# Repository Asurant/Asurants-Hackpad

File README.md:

# Asurants-Hackpad
A simple 6 key macropad meant for day to day usage.
Is capable of going back, forward, and refreshing a browser tab and is also capable of undoing, redoing, finding words (ctrl + f).

It was made using the Blueprint Hackpad tutorial from Hack Club.
https://blueprint.hackclub.com/r/56?ref=r

CAD Model:
The CAD Model Was made in Fusion 360\

Full CAD But Different Angle:\

CAD PCB No Case:\

CAD Model Without Top:\

CAD Model Bottom:\

CAD Model Top:\

Case Without PCB (Held Together by 4 M3x16mm screws):\

The PCB Was made in Kicad.

PCB Schematic:\

PCB:\

PCB 3D Model (From Kicad):\

The Firmware was done with QMK.
Key Shortcuts (Left to Right. Top To Bottom):
\[Browser Back, Browser Forward, Refresh]
\[Undo, Redo, Ctrl+F]

Bill of Materials:\
2x SK6812 MINI-E LEDs\
6x Cherry_MX switches\
6x DSA Keycaps\
4x M3x16mm Screws\
1x XIAO RP2040\
1x Case\

BTW\
Symbol on case is the Justiciar symbol from Lord Of The Mysteries / Lord Of Mysteries / Guǐ Mì Zhī Zhǔ

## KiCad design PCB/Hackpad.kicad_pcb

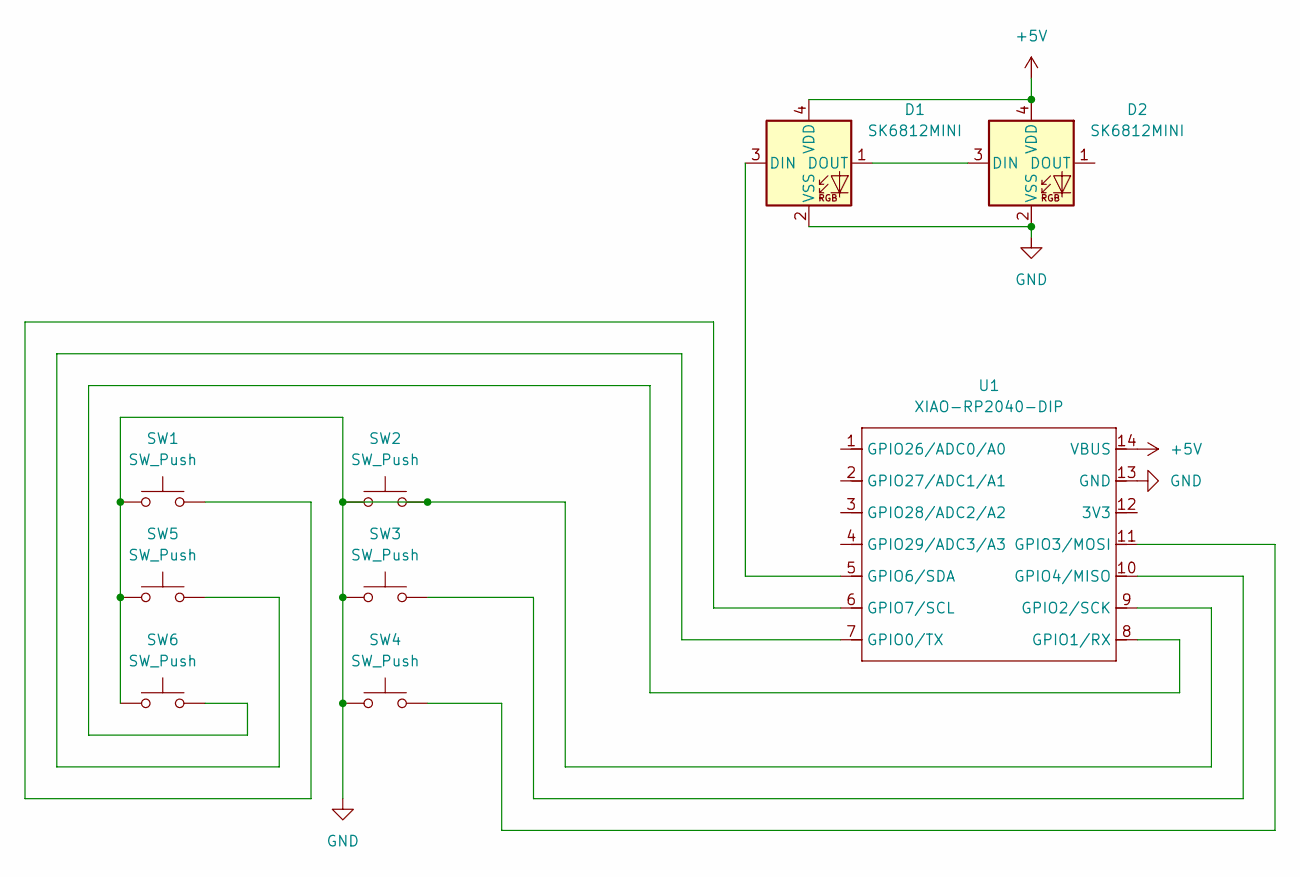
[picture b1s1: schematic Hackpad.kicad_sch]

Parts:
D1, D2: SK6812MINI; LED_SK6812MINI_PLCC4_3.5x3.5mm_P1.75mm
SW1, SW2, SW3, SW4, SW5, SW6: SW_Push; SW_Cherry_MX_1.00u_PCB
U1: XIAO-RP2040-DIP

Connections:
+5V: D1.4 (VDD), D2.4 (VDD), U1.14 (VBUS)
GND: D1.2 (VSS), D2.2 (VSS), SW1.1, SW2.1, SW2.2, SW3.1, SW4.1, SW5.1, SW6.1, U1.9 (GPIO2/SCK), U1.13 (GND)
unnamed: D1.3 (DIN), U1.5 (GPIO6/SDA)
unnamed: D1.1 (DOUT), D2.3 (DIN)
unnamed: SW5.2, U1.7 (GPIO0/TX)
unnamed: SW6.2, U1.8 (GPIO1/RX)
unnamed: SW4.2, U1.11 (GPIO3/MOSI)
unnamed: SW3.2, U1.10 (GPIO4/MISO)
unnamed: SW1.2, U1.6 (GPIO7/SCL)

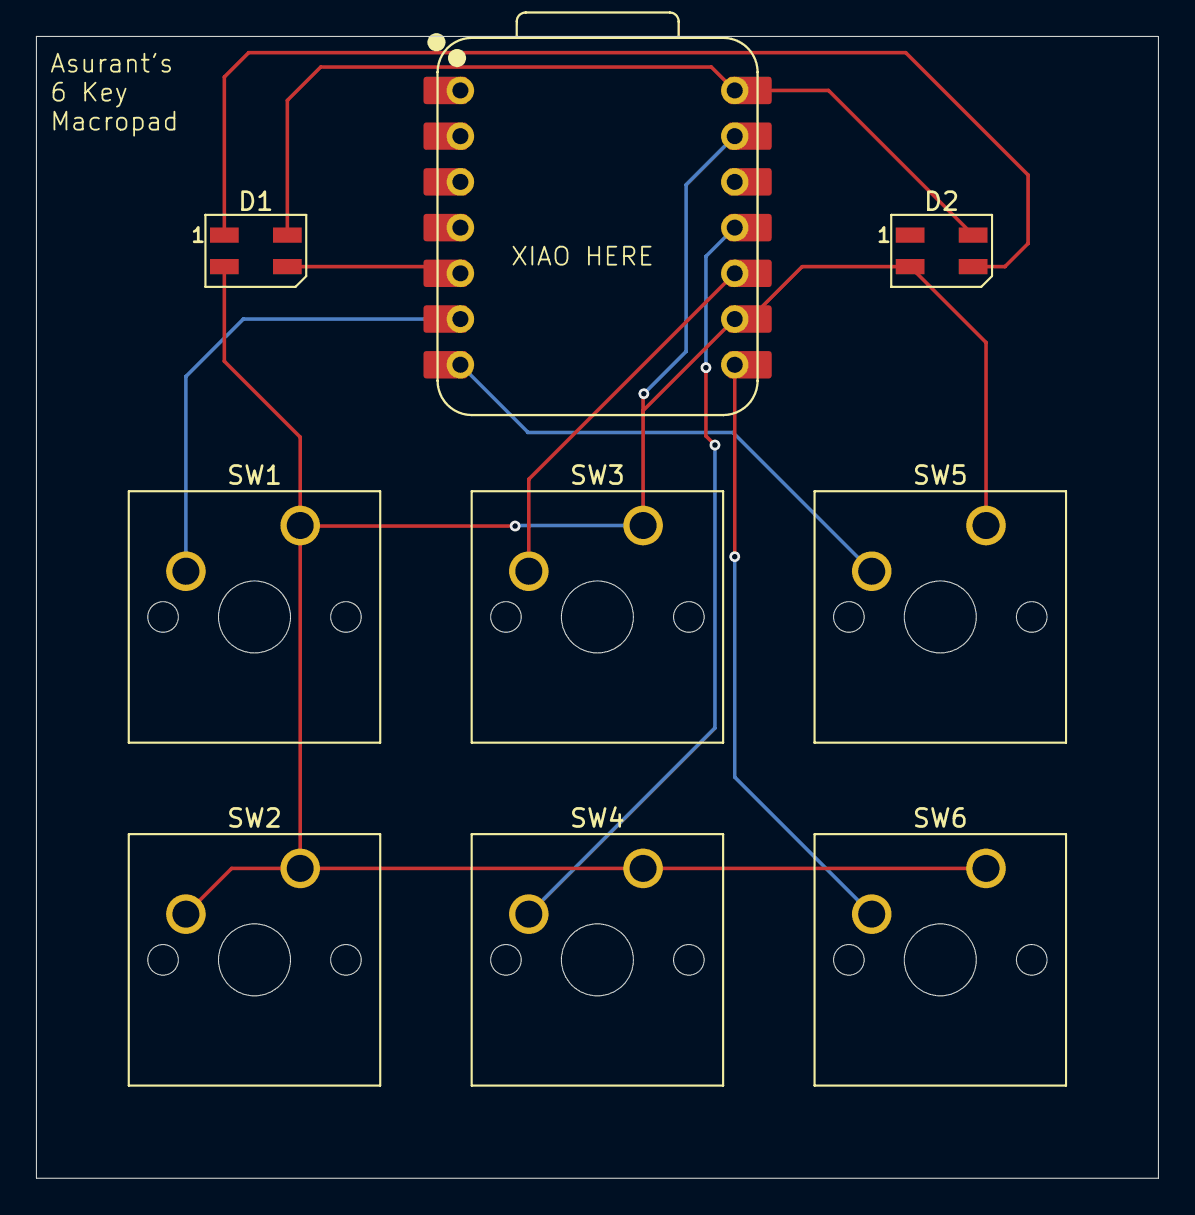
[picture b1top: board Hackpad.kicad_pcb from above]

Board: 2 copper layers, 62.3 x 63.4 mm, 9 parts (0 on the bottom side), 9 nets.

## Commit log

2025-11-20 Create temp
2025-11-20 Rename Full_Hackpad.step to CAD/Full_Hackpad.step
2025-11-20 Rename Hackpad.kicad_pro to Hackpad.kicad_pro
2025-11-20 Rename Hackpad Macros.json to Firmware/Hackpad Macros.json
2025-11-20 Update and rename Full_Hackpad.step to temp
